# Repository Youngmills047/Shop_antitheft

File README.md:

# Shop_antitheft
# Shop Anti-theft Device

## 1. Introduction
Retail theft leads to major losses, especially for small and medium-sized businesses. This project presents a **low-cost, portable, and smart anti-theft system** using proximity sensing and wireless communication to alert staff of suspicious activity near shelves or exits.

## 2. Objectives
- Detect unauthorized hand movements or object removals.
- Provide loud alarm notifications.
- Enable optional wireless alerts via Wi-Fi or Bluetooth.
- Ensure portability with a rechargeable battery.

## 3. System Components
### 🔌 Microcontroller: ESP32-WROOM-32
- Reads sensor data and controls the system.
- Enables wireless notifications via Wi-Fi/Bluetooth.

### 📡 Proximity Sensor: VL53L0X or VL53L1X
- Time-of-Flight sensor to detect motion and proximity changes.

### 🔊 Alarm: Buzzer with PAM8302 Driver
- Loud audio output for instant alert.

### 🔋 Power Supply
- TP4057-based Li-ion battery charger.
- MP1584 / LM2576HVS regulator to power 3.3V devices.
- USB-C input for charging.

### 🧰 Debug Header
- UART + I²C access for firmware updates and calibration.

## 4. Operation
1. **Monitoring Mode:** Continuously checks proximity.
2. **Detection:** Flags sudden object removal or movement.
3. **Alarm:** Triggers loud buzzer.
4. **Optional:** Sends a wireless notification via Wi-Fi.
5. **Portable:** Battery-powered, no installation hassle.

## 5. Features
- 🔋 Rechargeable and portable
- 📢 Loud audible alarm
- 🌐 Wi-Fi/Bluetooth notification support
- 🛠️ Simple deployment
- 🔄 Low power consumption

## 6. Applications
- Retail and convenience stores
- Bookshops, pharmacies
- Temporary setups like kiosks or exhibitions

## 7. Conclusion
This device offers an easy-to-install, cost-effective alternative to expensive surveillance systems. By integrating modern sensing and IoT technology, it provides real-time theft deterrence for shops of all sizes.

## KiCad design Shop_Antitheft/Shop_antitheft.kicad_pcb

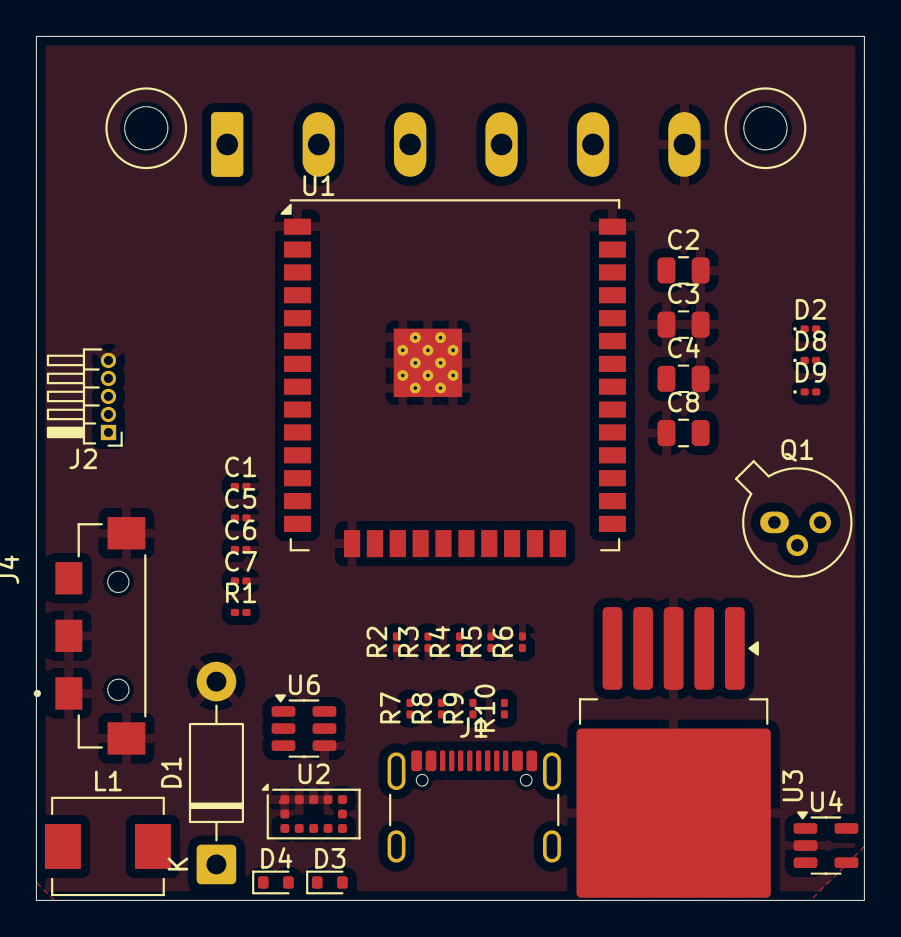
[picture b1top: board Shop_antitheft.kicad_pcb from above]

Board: 2 copper layers, 46.0 x 48.0 mm, 35 parts (1 on the bottom side), 29 nets, no tracks yet.

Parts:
C1, C5, C7: 10uF; C_0201_0603Metric
C2, C8: 10uF; C_0805_2012Metric
C3: 100uF; C_0805_2012Metric
C4: 1000uF; C_0805_2012Metric
C6: 100nF; C_0201_0603Metric
D1: 1N47xxA; D_DO-41_SOD81_P10.16mm_Horizontal
D2: D; D_0201_0603Metric
D3, D4: 1N4148WT; D_SOD-523
D8, D9: LED; LED_0201_0603Metric
J1: USB_C_Receptacle_USB2.0_14P; USB_C_Receptacle_GCT_USB4105-xx-A_16P_TopMnt_Horizontal
J2: Conn_01x05_MountingPin; PinHeader_1x05_P1.00mm_Horizontal
J3: Conn_01x06_Socket; PhoenixContact_MC_1,5_6-GF-5.08_1x06_P5.08mm_Horizontal_Thr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
J4: 1746142-1; TE_1746142-1
L1: 100uH; L_Neosid_SM-PIC0512H
Q1: BC107; TO-18-3
R1, R8: 2k; R_0201_0603Metric
R2, R3, R4, R7, R9, R10: 10k; R_0201_0603Metric
R5: 5.1k; R_0201_0603Metric
R6: 1k; R_0201_0603Metric
U1: ESP32-WROOM-32U
U2: VL53L0CXV0DH1; ST_VL53L1x
U3: LM2576HVS-3.3; TO-263-5_TabPin3
U4: TP4057; TSOT-23-5
U6: PAM8302AAD; SOT-23-6

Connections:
+3.3V: C1.1, C4.1, C7.1, L1.2, Q1.3 (C), R1.2, R8.2, R9.2, R10.1, U1.2 (VDD), U2.11 (AVDD), U3.4 (FB)
/D1: J3.3, U1.28 (IO17)
/EN: J2.4, U1.3 (EN)
/GPIO1: R10.2, U1.26 (IO4), U2.7 (GPIO1)
/IO01: J2.3, U1.25 (IO0)
/IO15: U1.23 (IO15), U6.1 (~SD)
/PM: C6.1, Q1.1 (E), U6.6 (VDD)
/RST: J3.4, U1.27 (IO16)
/RXD: J2.2, U1.34 (RXD0/IO3)
/SCL: J3.2, R8.1, U1.20 (SCK/CLK), U2.10 (SCL)
/SDA: R1.1, U1.21 (SDO/SD0), U2.9 (SDA)
/SDA_1: J3.1, U1.22 (SDI/SD1)
/TXD: J2.1, U1.35 (TXD0/IO1)
/VBAT: C8.2, D4.1 (K), R7.2, U3.1 (VIN)
/VBUS: C2.1, D8.2 (A), D9.2 (A), R4.2, U4.4 (V_{CC})
/XSHUT: R9.1, U1.29 (IO5), U2.5 (XSHUT)
GND: C1.2, C2.2, C3.1, C3.2, C4.2, C5.2, C6.2, C7.2, C8.1, D1.2 (A), J2.5, J3.6, J4.1, J4.2, J4.SH1 (SHIELD1), J4.SH2 (SHIELD2), R2.1, R3.1, R5.2, R6.2, U1.1 (GND), U1.15 (GND), U1.38 (GND), U1.39 (GND), U2.1 (AVDDVCSEL), U2.2 (AVSSVCSEL), U2.3 (GND), U2.4 (GND), U2.6 (GND), U2.12 (GND), U3.3 (GND), U4.2 (GND), U6.4 (IN-)
unnamed: D1.1 (K), L1.1, U3.2 (OUT)
unnamed: D2.2 (A), J1.A4 (VBUS), J1.A9 (VBUS), J1.B4 (VBUS), J1.B9 (VBUS)
unnamed: D2.1 (K), R4.1
unnamed: C5.1, D3.2 (A), U4.3 (BAT)
unnamed: D3.1 (K), D4.2 (A), J4.3
unnamed: D8.1 (K), U4.1 (~CHRG)
unnamed: D9.1 (K), U4.5 (STDBY)
unnamed: J1.A5 (CC1), R5.1
unnamed: J1.A1 (GND), J1.A12 (GND), J1.B1 (GND), J1.B12 (GND), R3.2
unnamed: J1.S1 (SHIELD), R2.2
unnamed: Q1.2 (B), U1.16 (IO13)
unnamed: R7.1, U3.5 (~ON/OFF)
